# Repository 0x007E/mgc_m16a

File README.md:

# `MGC_module` - ATmega16A

The `ATmega16A` (`mgc_module`) is an adaptable board for the [MeGARCard](https://github.com/0x007e/mgc). The board offers the possibility to control the `MeGARCard` with an [ATmega16A](#additional-information). The board itself is connected to the `MeGARCard` within the pcb-to-pcb connectors (no soldering necessary). With the onboard dip-switches the board voltage can be regulated from `3V3` to `5V`. Also the usage of hardware-/software-`twi` to control the [SSD1306](#additional-information)-display on the megacard can be selected.

> To mount the board on the `MeGARCard` disconnect the power source (`USB-C` connector) or any other used source from the MeGARCard!

| Experience  | Level                                                                               |
|:------------|:-----------------------------------------------------------------------------------:|
| Soldering   |  |

# Downloads

| Type      | File                                                                                                                                                 | Description     |
|:---------:|:----------------------------------------------------------------------------------------------------------------------------------------------------:|:----------------|
| Schematic | [pdf](https://github.com/0x007E/mgc_m16a/releases/latest/download/schematic.pdf) / [cadlab](https://cadlab.io/project/30414/main/files)                   | Schematic files |
| Board     | [pdf](https://github.com/0x007E/mgc_m16a/releases/latest/download/pcb.pdf) / [cadlab](https://cadlab.io/project/30414/main/files)                         | Board file      |
| Drill     | [pdf](https://github.com/0x007E/mgc_m16a/releases/latest/download/drill.pdf)                                                                              | Drill file      |
| BoM | [xlsx](https://github.com/0x007E/mgc_m16a/releases/latest/download/bom.xlsx) / [html](https://github.com/0x007E/mgc_m16a/releases/latest/download/ibom.html)          | Bill of Material as Excel/interactive HTML |
| PCB    | [zip](https://github.com/0x007E/mgc_m16a/releases/latest/download/kicad.zip) / [tar](https://github.com/0x007E/mgc_m16a/releases/latest/download/kicad.tar.gz)    | KiCAD/Gerber/BoM/Drill files       |

# Hardware

The pcb is created with `KiCAD`. All files are built with `github actions` so that they are ready for a production environment.

## PCB

The circuit board is populated on both sides (Top, Bottom). The best way for soldering the `SMD` components is within a vapor phase soldering system and for the `THT` components with a standard soldering system.

### Top Layer

### Bottom Layer

# Additional Information

| Type       | Link               | Description              |
|:----------:|:------------------:|:-------------------------|
| ATmega16A  | [pdf](https://ww1.microchip.com/downloads/en/devicedoc/atmel-8154-8-bit-avr-atmega16a_datasheet.pdf) | 8-bit Microcontroller with 16K Bytes In-System Programmable Flash |
| SSD1306 | [pdf](https://www.vishay.com/docs/37902/oled128o064dbpp3n00000.pdf) | 128 x 64 Graphic OLED |

---

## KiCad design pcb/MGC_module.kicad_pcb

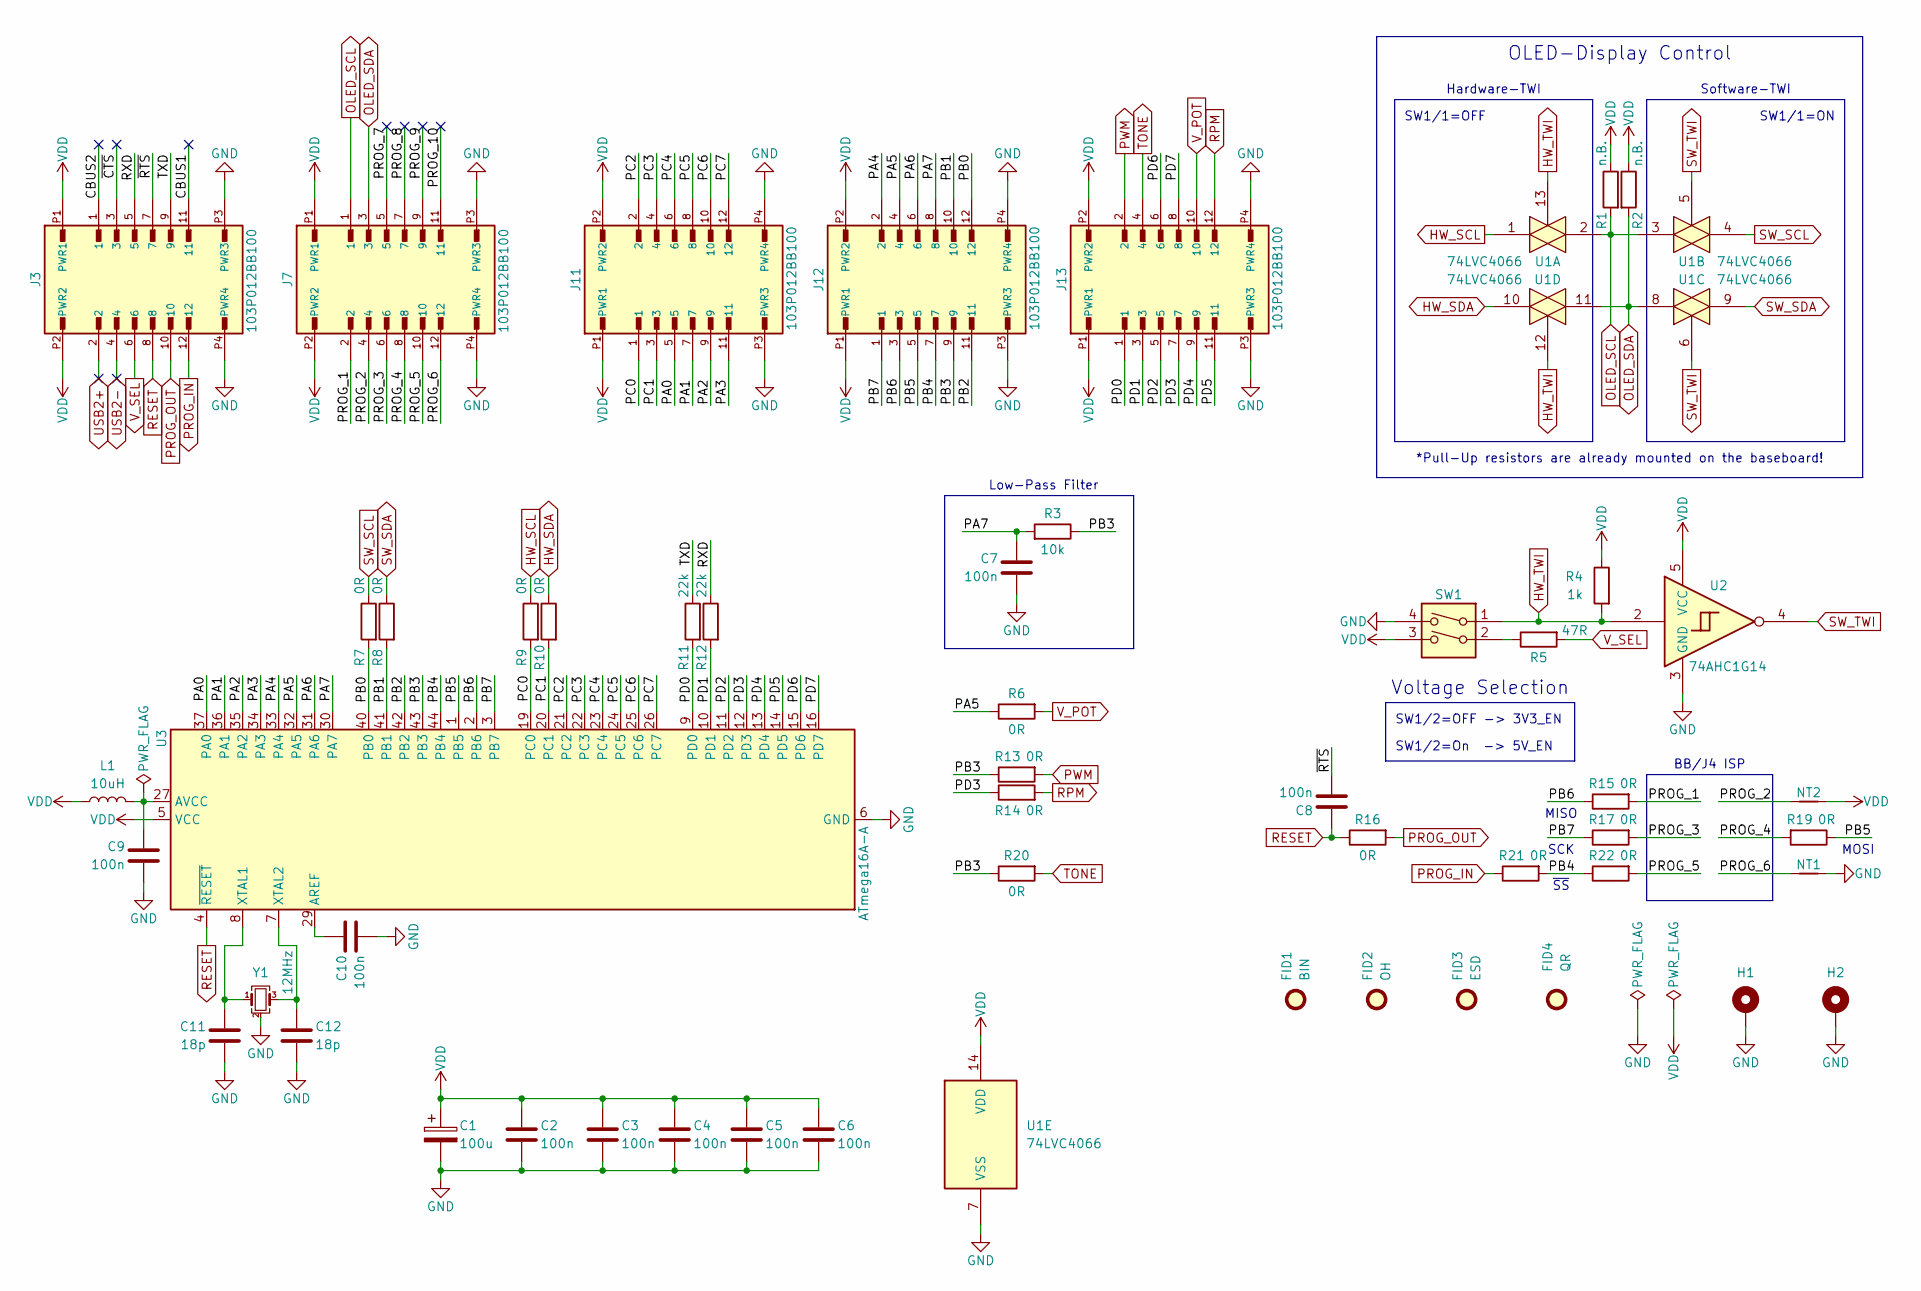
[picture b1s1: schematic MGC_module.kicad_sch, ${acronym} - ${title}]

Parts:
C1: 100u; CP_EIA-3528-21_Kemet-B; DigiKey 478-3877-1-ND
C2, C3, C4, C5, C6, C7, C8, C9, C10: 100n; C_1206_3216Metric
C11, C12: 18p; C_0805_2012Metric
FID1: BIN; WEEE-Logo_4.2x6mm_SilkScreen
FID2: OH; OSHW-Logo2_7.3x6mm_SilkScreen
FID3: ESD; ESD-Logo_6.6x6mm_SilkScreen
FID4: QR; QR_0x007e_very_small
H1, H2: MountingHole_Pad; MountingHole_2.7mm_M2.5_DIN965_Pad
J3, J7, J11, J12, J13: 103P012BB100; AMPHENOL_103P012BB100; DigiKey 609-103P012BB100CT-ND
L1: 10uH; L_1206_3216Metric
NT1, NT2: NetTie_2; NetTie-2_SMD_Pad0.5mm
R1, R2: n.B.; R_1206_3216Metric
R3: 10k; R_1206_3216Metric
R4: 1k; R_1206_3216Metric
R5: 47R; R_1206_3216Metric
R6, R7, R8, R9, R10, R13, R14, R15, R16, R17, R19, R20, R21, R22: 0R; R_1206_3216Metric
R11, R12: 22k; R_1206_3216Metric
SW1: SW_DIP_x02; SW_DIP_SPSTx02_Slide_6.7x6.64mm_W6.73mm_P2.54mm_LowProfile_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
U1: 74LVC4066; SO-14_3.9x8.65mm_P1.27mm; DigiKey 1727-6368-1-ND
U2: 74AHC1G14; SOT-23-5
U3: ATmega16A-A; TQFP-44_10x10mm_P0.8mm
Y1: 12MHz; Crystal_SMD_Abracon_ABM8AIG-4Pin_3.2x2.5mm

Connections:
/CBUS1: J3.11
/CBUS2: J3.1
/PA0: J11.5, U3.37 (PA0)
/PA1: J11.7, U3.36 (PA1)
/PA2: J11.9, U3.35 (PA2)
/PA3: J11.11, U3.34 (PA3)
/PA4: J12.2, U3.33 (PA4)
/PA5: J12.4, R6.1, U3.32 (PA5)
/PA6: J12.6, U3.31 (PA6)
/PA7: C7.1, J12.8, R3.2, U3.30 (PA7)
/PB0: J12.12, R7.2, U3.40 (PB0)
/PB1: J12.10, R8.2, U3.41 (PB1)
/PB2: J12.11, U3.42 (PB2)
/PB3: J12.9, R3.1, R13.1, R20.1, U3.43 (PB3)
/PB4: J12.7, R21.2, R22.1, U3.44 (PB4)
/PB5: J12.5, R19.1, U3.1 (PB5)
/PB6: J12.3, R15.1, U3.2 (PB6)
/PB7: J12.1, R17.1, U3.3 (PB7)
/PC0: J11.1, R9.2, U3.19 (PC0)
/PC1: J11.3, R10.2, U3.20 (PC1)
/PC2: J11.2, U3.21 (PC2)
/PC3: J11.4, U3.22 (PC3)
/PC4: J11.6, U3.23 (PC4)
/PC5: J11.8, U3.24 (PC5)
/PC6: J11.10, U3.25 (PC6)
/PC7: J11.12, U3.26 (PC7)
/PD0: J13.1, R11.2, U3.9 (PD0)
/PD1: J13.3, R12.2, U3.10 (PD1)
/PD2: J13.5, U3.11 (PD2)
/PD3: J13.7, R14.1, U3.12 (PD3)
/PD4: J13.9, U3.13 (PD4)
/PD5: J13.11, U3.14 (PD5)
/PD6: J13.6, U3.15 (PD6)
/PD7: J13.8, U3.16 (PD7)
/PROG_1: J7.2, R15.2
/PROG_2: J7.4, NT2.1
/PROG_3: J7.6, R17.2
/PROG_4: J7.8, R19.2
/PROG_5: J7.10, R22.2
/PROG_6: J7.12, NT1.1
/PROG_7: J7.5
/PROG_8: J7.7
/PROG_9: J7.9
/PROG_10: J7.11
/RXD: J3.5, R12.1
/TXD: J3.9, R11.1
/~CTS: J3.3
/~RTS: C8.2, J3.7
GND: C1.2, C2.2, C3.2, C4.2, C5.2, C6.2, C7.2, C9.2, C10.2, C11.2, C12.2, H1.1, H2.1, J3.P3 (PWR3), J3.P4 (PWR4), J7.P3 (PWR3), J7.P4 (PWR4), J11.P3 (PWR3), J11.P4 (PWR4), J12.P3 (PWR3), J12.P4 (PWR4), J13.P3 (PWR3), J13.P4 (PWR4), NT1.2, SW1.4, U1.7 (VSS), U2.3 (GND), U3.6 (GND), U3.18 (GND), U3.28 (GND), U3.39 (GND), Y1.2 (G), Y1.4 (G)
HW_SCL: R9.1, U1.1
HW_SDA: R10.1, U1.10
HW_TWI: R4.2, SW1.1, U1.12, U1.13, U2.2
unnamed: R5.1, SW1.2
unnamed: C10.1, U3.29 (AREF)
unnamed: C9.1, L1.2, U3.27 (AVCC)
unnamed: C11.1, U3.8 (XTAL1), Y1.1
unnamed: C12.1, U3.7 (XTAL2), Y1.3
OLED_SCL: J7.1, R1.2, U1.2, U1.3
OLED_SDA: J7.3, R2.2, U1.8, U1.11
PROG_IN: J3.12, R21.1
PROG_OUT: J3.10, R16.2
PWM: J13.2, R13.2
RESET: C8.1, J3.8, R16.1, U3.4 (~RESET)
RPM: J13.12, R14.2
SW_SCL: R7.1, U1.4
SW_SDA: R8.1, U1.9
SW_TWI: U1.5, U1.6, U2.4
TONE: J13.4, R20.2
USB2+: J3.2
USB2-: J3.4
VDD: C1.1, C2.1, C3.1, C4.1, C5.1, C6.1, J3.P1 (PWR1), J3.P2 (PWR2), J7.P1 (PWR1), J7.P2 (PWR2), J11.P1 (PWR1), J11.P2 (PWR2), J12.P1 (PWR1), J12.P2 (PWR2), J13.P1 (PWR1), J13.P2 (PWR2), L1.1, NT2.2, R1.1, R2.1, R4.1, SW1.3, U1.14 (VDD), U2.5 (VCC), U3.5 (VCC), U3.17 (VCC), U3.38 (VCC)
V_POT: J13.10, R6.2
V_SEL: J3.6, R5.2

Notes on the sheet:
SW1/2=OFF -> 3V3_EN
SW1/1=OFF
MOSI
SW1/2=On -> 5V_EN
*Pull-Up resistors are already mounted on the baseboard!
~{SS}
OLED-Display Control
Low-Pass Filter
Voltage Selection
SCK
SW1/1=ON
MISO
BB/J4 ISP
Hardware-TWI
Software-TWI

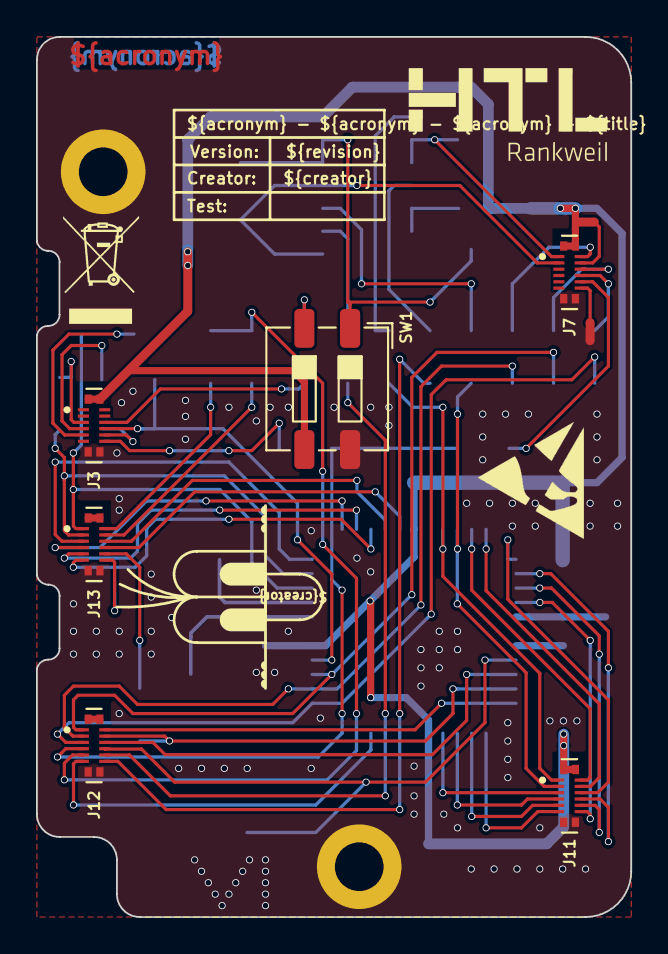
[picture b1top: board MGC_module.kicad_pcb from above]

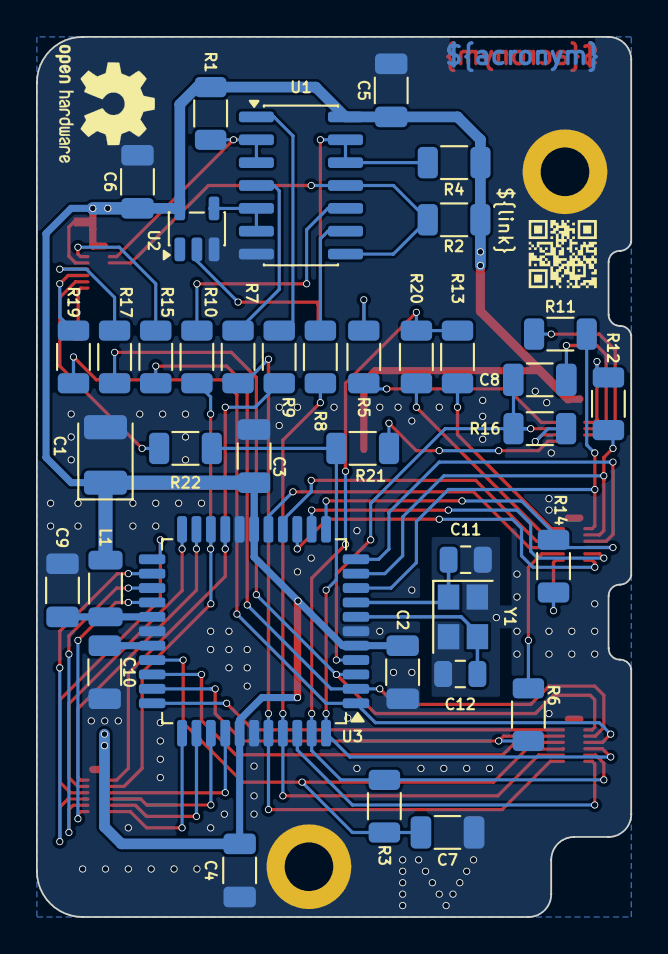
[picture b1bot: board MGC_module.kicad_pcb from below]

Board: 2 copper layers, 33.0 x 48.9 mm, 52 parts (40 on the bottom side), 64 nets.

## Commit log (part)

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2026-06-10 Add pcb layout
2026-06-11 Update uart series resistor values
2026-06-12 Decrease font size of cu acronym
2026-06-17 Adapt VDD traces
2026-06-17 Add README.md
2026-06-17 Add build pipeline
2026-06-17 Add release pipeline
2026-06-23 Adapt output filenames
2026-06-23 Add missing values in bom
2026-06-23 Adapt config and update action versions

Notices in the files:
README.md:
License CC By-NC-SA
parts and their libraries:
license: CC BY-NC-SA 4.0
